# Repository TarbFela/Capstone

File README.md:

# A Temperature Programming Power & Control System for Desorption Energy Measurement Experiments

This is my electrical & computer engineering capstone as well as my honors thesis at the University of Maine. The hardware includes a number of power cards driven by PWM signals from a control board. Another board provides a serial interface to a Balzers mass spectrometer QMS 112 interface. The software for this project is largely written for the RP2350 microcontroller (like that found on the Raspberry Pi Pico 2) on a Pimoroni PGA2350 devboard/daughtercard. The PGA2350 plugs into the controller motherboard called ADPC for "Analog and Digital Processing and Control". This board incorporates, in addition to other instrumentation, MCP3462R and MCP3562R ADCs and an ADA4255 PGIA; all three of these provide SPI interfaces. I'm writing drivers for these devices which can be found in `src2/`. Functionalities are loosely (and currently rather haphazardly, with deprecation, poor compartmentalization, etc) broken out into separate headers/source files. 

I'll probably post hardware files somewhere at some point. The READMEs are currently acting as in-progress note-taking and as in-progress documentation. This project is meant to be used after I graduate by researchers in the Frederick Lab at FIRST. The code is roughly written with extensibility in mind.

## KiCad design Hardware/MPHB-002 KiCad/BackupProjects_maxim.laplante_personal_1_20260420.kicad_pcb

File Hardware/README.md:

# Temperature Programming & Control System Hardware

This is a collection of hardware documentation and resources. EasyEDA projects are downloaded and have been parsed by KiCad (do _not_ attempt to fabricate from these KiCad projects; fonts, etc have _not_ carried over). All datasheets used have been added. Any written hardware documentation is included.

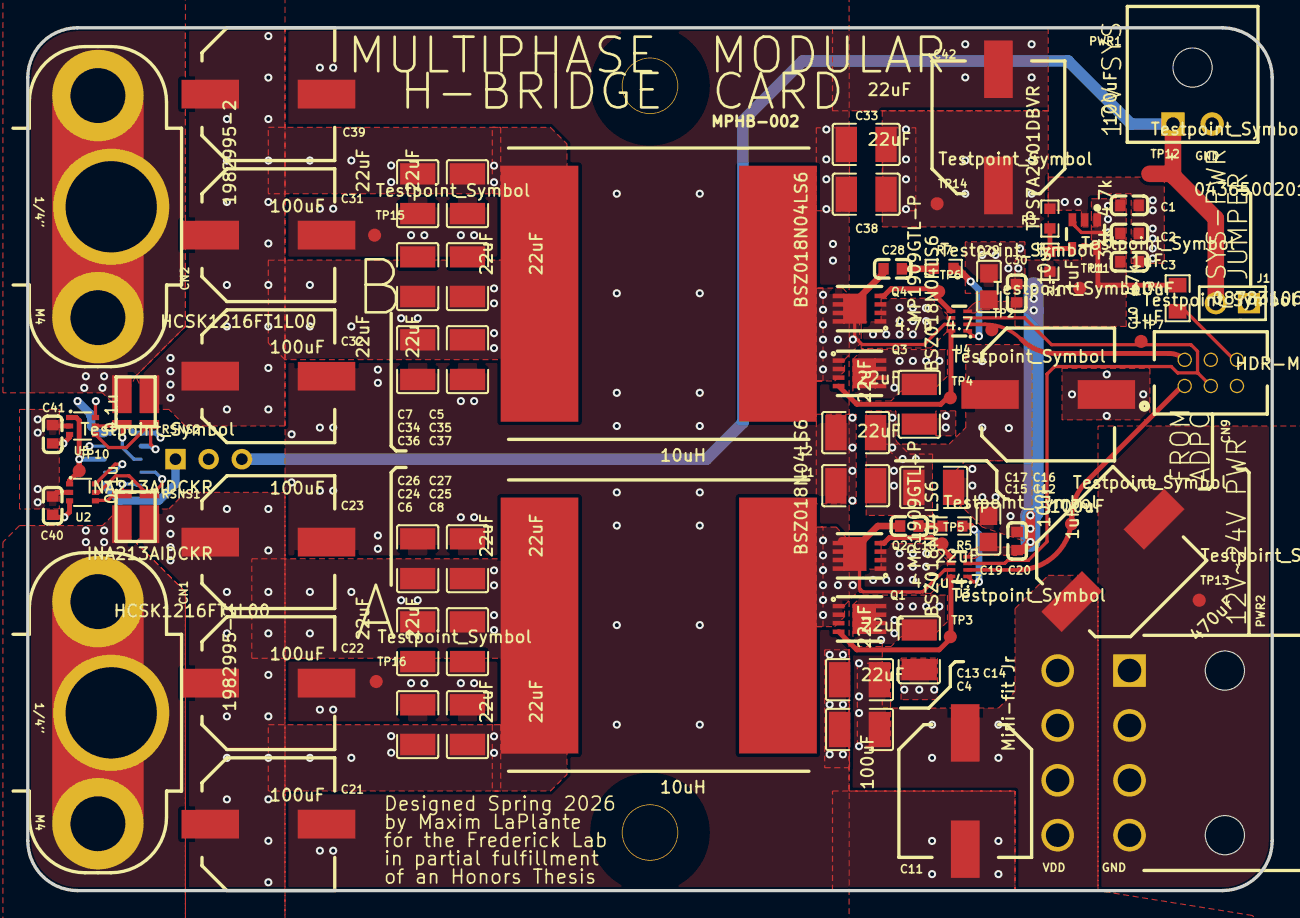
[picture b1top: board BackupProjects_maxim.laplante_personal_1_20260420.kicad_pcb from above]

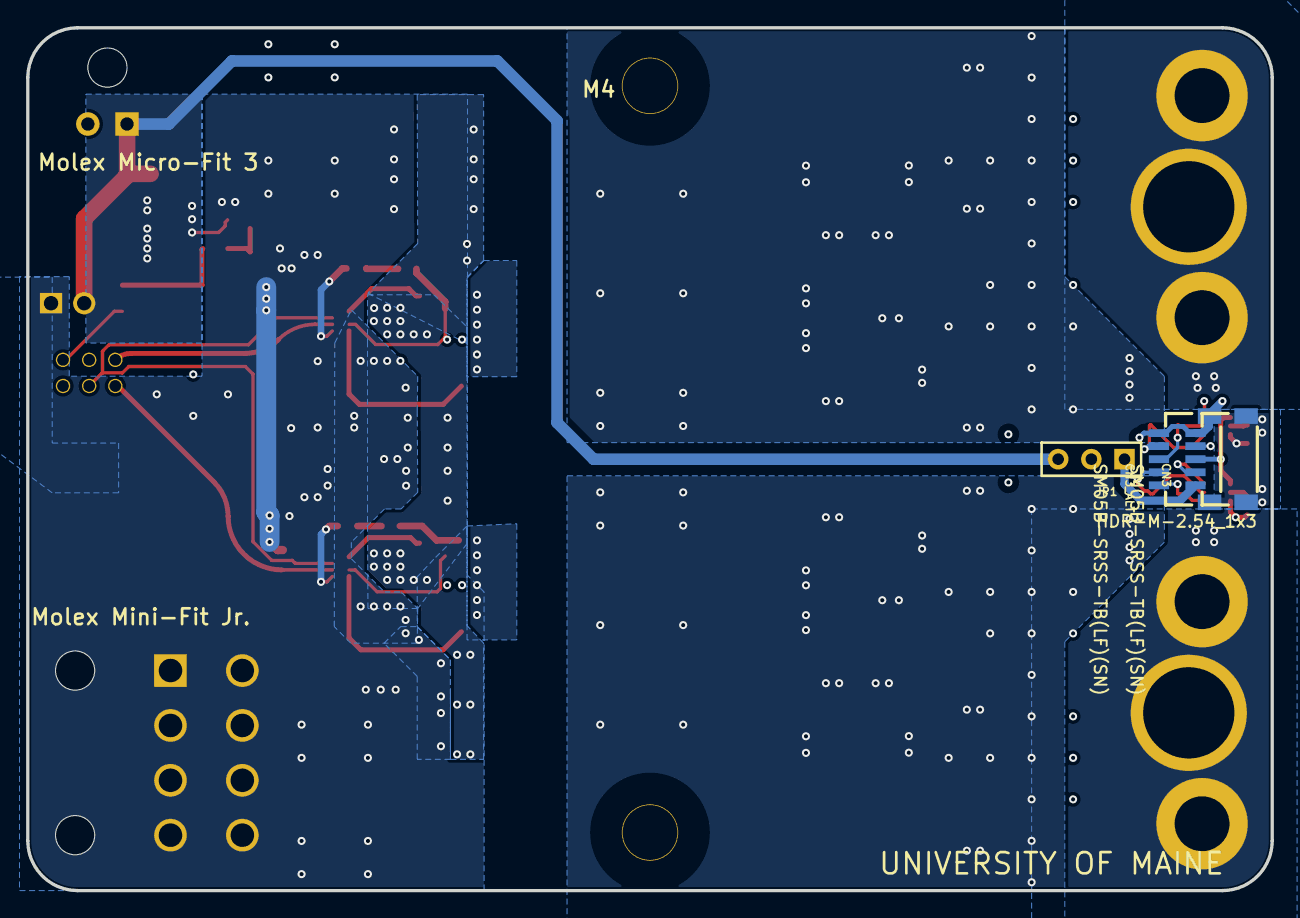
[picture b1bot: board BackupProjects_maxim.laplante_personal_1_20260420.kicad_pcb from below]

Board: 4 copper layers, 95.2 x 66.0 mm, 87 parts (3 on the bottom side), 32 nets.

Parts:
C1, C3, C20, C30: 1uF; C0603
C2: 10uF; C0603
C4, C5, C6, C7, C8, C12, C13, C14, C15, C16, C17, C24, C25, C26, C27, C33, C34, C35, C36, C37, C38: 22uF; C1210
C9: 470uF; APD_CAP_1012
C10, C11, C21, C22, C23, C31, C32, C39, C42: 100uF; APD_CAP_1012
C18, C28: 4.7u; C0603
C19, C29: 10uF; C0805
C40, C41: 0.1u; C0603
CN1, CN2: 1982995-2
CN3, CN3_ALT: SM05B-SRSS-TB(LF)(SN); CONN-SMD_SM05B-SRSS-TB
CN9: 0878310641
J1: HDR-M-2.54_1x2; HDR-M-2.54_1X2
JP1: HDR-M-2.54_1x3; HDR-M-2.54_1X3
L1, L2: 10uH; SRP2313AA
PWR1: 0436500201
PWR2: Mini-fit Jr; 0039301080
Pad_gge22614: Pad_gge22614
Pad_gge22653: Pad_gge22653
Pad_gge24533: Pad_gge24533
Pad_gge33304: Pad_gge33304
Q1, Q2, Q3, Q4: BSZ018N04LS6; PG-TSDSON-8_L3.3-W3.3-P0.65-BL
R1: 33k; R0603
R3: 4.7k; R0603
R4: 47k; R0805
R5, R7: 4.7; R0603
RSNS1, RSNS2: HCSK1216FT1L00; HCSK1216
TP1, TP2, TP3, TP4, TP5, TP6, TP7, TP10, TP11, TP12, TP13, TP14, TP15, TP16: Testpoint_Symbol; TP_TOUCH
U1: TPS7A2401DBVR; SOT-23-5_L2.9-W1.6-P0.95-LS2.8-BR
U2, U5: INA213AIDCKR; TSSOP-6_L2.0-W1.3-P0.65-LS2.0-BR
U3, U4: MP1909GTL-P; SOT-583-8_L2.1-W1.6-P0.50-LS1.6-BL

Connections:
A_OUT: CN1.1, RSNS1.2
A_OUT_FILT: C6.2, C8.2, C21.P, C22.P, C23.P, C24.2, C25.2, C26.2, C27.2, L1.2, RSNS1.1
A_SNS_HI: CN3_ALT.2, RSNS1.3, U2.5
A_SNS_LO: CN3_ALT.1, RSNS1.4, U2.4
B_OUT: CN2.1, RSNS2.1
B_OUT_FILT: C5.2, C7.2, C31.P, C32.P, C34.2, C35.2, C36.2, C37.2, C39.P, L2.2, RSNS2.2
B_SNS_HI: CN3_ALT.4, RSNS2.4, U5.4
B_SNS_LO: CN3_ALT.3, RSNS2.3, U5.5
C28_1: C28.1, R7.2
CN9_6: CN9.6, R4.1
DRVH_A: Q1.4, TP3.1, U3.8
DRVL_A: Q2.4, TP5.1, U3.5
GD_PWM_A: CN9.1, TP1.1, U3.2
GD_PWM_C: CN9.2, TP2.1, U4.2
GND: C1.1, C2.1, C3.1, C4.1, C5.1, C6.1, C7.1, C8.1, C9.N, C10.N, C11.N, C12.1, C13.1, C14.1, C15.1, C16.1, C17.1, C19.1, C20.1, C21.N, C22.N, C23.N, C24.1, C25.1, C26.1, C27.1, C29.1, C30.1, C31.N, C32.N, C33.1, C34.1, C35.1, C36.1, C37.1, C38.1, C39.N, C40.1, C41.1, C42.N, CN3.5, CN3.6, CN3.7, CN3_ALT.5, CN3_ALT.6, CN3_ALT.7, CN9.4, PWR1.2, PWR2.1, PWR2.2, PWR2.3, PWR2.4, Q2.1, Q2.2, Q2.3, Q4.1, Q4.2, Q4.3, R3.1, TP13.1, TP15.1, TP16.1, U1.2, U2.2, U3.6, U4.6, U5.2
HIGH_GATE_C: Q3.4, TP4.1, U4.8
I_SNS_A_OUT: CN3.2, U2.6
I_SNS_B_OUT: CN3.4, U5.6
I_SNS_REF_IN: CN3.3, TP10.1, U2.1, U5.1
I_SNS_VCC: C40.2, C41.2, JP1.2, U2.3, U5.3
I_SNS_VCC_IN: CN3.1, JP1.1
LOW_GATE_C: Q4.4, TP6.1, U4.5
PH_EN: CN9.3, TP7.1, U3.3, U4.3
R5_2: C18.1, R5.2
R7_1: R7.1, U4.1
REG_FB: R1.1, R3.2, U1.4
SW_A: C18.2, L1.1, Q1.1, Q1.2, Q1.3, Q2.5, Q2.6, Q2.7, Q2.8, Q2.9, U3.7
SW_C: C28.2, L2.1, Q3.1, Q3.2, Q3.3, Q4.5, Q4.6, Q4.7, Q4.8, Q4.9, U4.7
U3_1: R5.1, U3.1
VCC: C1.2, C2.2, J1.2, JP1.3, PWR1.1, TP12.1, U1.1, U1.3
VDD: C4.2, C9.P, C10.P, C11.P, C12.2, C13.2, C14.2, C15.2, C16.2, C17.2, C33.2, C38.2, C42.P, J1.1, PWR2.5, PWR2.6, PWR2.7, PWR2.8, Q1.5, Q1.6, Q1.7, Q1.8, Q1.9, Q3.5, Q3.6, Q3.7, Q3.8, Q3.9, TP14.1
V_GDRV: C3.2, C19.2, C20.2, C29.2, C30.2, R1.2, R4.2, TP11.1, U1.5, U3.4, U4.4

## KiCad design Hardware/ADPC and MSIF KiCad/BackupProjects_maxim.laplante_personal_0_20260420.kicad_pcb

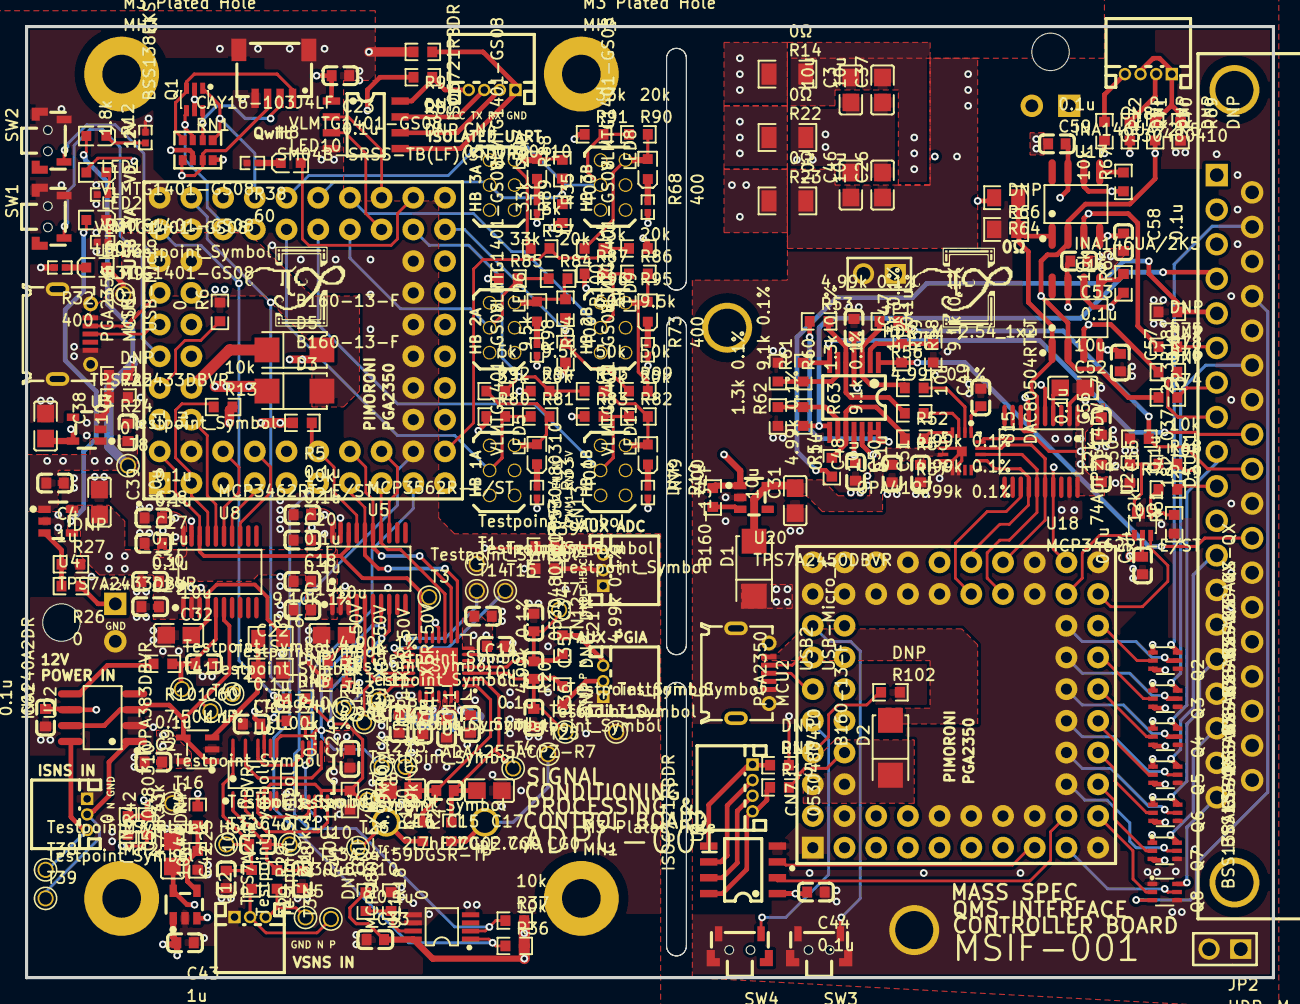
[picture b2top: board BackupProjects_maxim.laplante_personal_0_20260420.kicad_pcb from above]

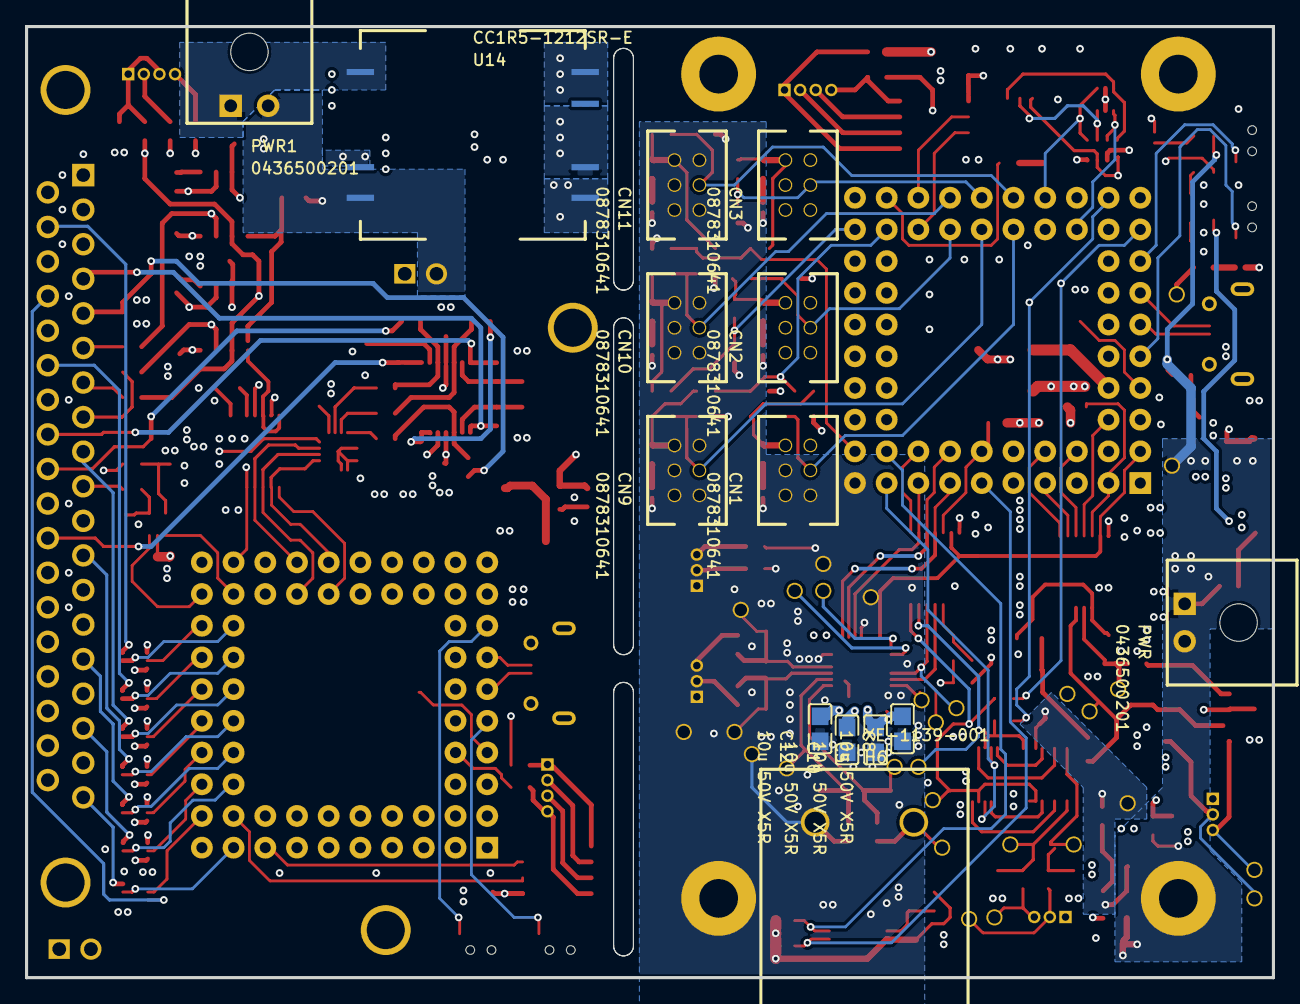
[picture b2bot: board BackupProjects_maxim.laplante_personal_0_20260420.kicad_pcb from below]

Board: 4 copper layers, 99.9 x 76.2 mm, 269 parts (14 on the bottom side), 217 nets.

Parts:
C1, C4, C43: 1u; C0603
C2, C13, C18, C19, C20, C21, C23, C24, C27, C28, C29, C30, C33, C44, C45, C47, C48, C51, C53, C54, C55, C56, C57, C58, C59, C61: 0.1u; C0603
C3, C25, C26, C31, C37, C38, C39, C46, C52: 10u; C0805
C5, C8, C10, C12: 10u 50V X5R; C0805
C6, C7, C9, C11: 0.1u X5R 50V; C0603
C14, C22, C32, C49, C50: 10u; C0603
C15: 270pF CG0; C0603
C16, C17: 2.7nF CG0; C0805
C34, C35, C36: DNP; C0603
C40, C60: 1nF; C0603
C41, C42: 10nF; C0603
CN1, CN2, CN3, CN9, CN10, CN11: 0878310641
CN4, CN7, CN8: 0530480410; CONN-TH_8P-P1.25_0530480610
CN5, CN6, CN12, CN13: 0530480310; CONN-TH_8P-P1.25_0530480410
D1, D2, D3, D5: B160-13-F; SMA_L4.3-W2.6-LS5.2-RD
DSUB1: 182-037-213R181; DB37-TH_182-037-213R181
H6: XE-1139-001; CONN-TH_XE-1139-001
H8: SM04B-SRSS-TB(LF)(SN)(P); CONN-SMD_4P-P1.00_SM04B-SRSS-TB-LF-SN
JP1, JP2: HDR-M-2.54_1x2; HDR-M-2.54_1X2
LED1, LED2, LED3, LED4, LED5, LED6, LED7, LED8, LED9, LED10, LED11: VLMTG1401-GS08; LED0603-RD_GREEN
MCU1, MCU2: PGA2350
MH1, MH2, MH3, MH4: M3 Plated Hole; M3 PLATED HOLE
PWR, PWR1: 0436500201
Pad_gge97344: Pad_gge97344
Pad_gge97365: Pad_gge97365
Q1: BSS138BKS,115; SOT-363_L2.0-W1.3-P0.65-LS2.1-BR
Q2, Q3, Q4, Q5, Q6, Q7, Q8: BSS138AKS-QX; SOT-363_L2.1-W1.3-P0.65-LS2.1-BL
R1, R2, R20, R21, R52, R53, R54, R55, R56, R57: 4.99k 0.1%; R0603
R3, R4: 4.90k 1%; R0603
R5, R13, R36, R37, R48, R49, R65, R67: 10k; R0603
R6, R18, R39, R47: 0; R0603_NEW
R8, R9, R11, R15, R19, R40, R43, R102: DNP; R0603_NEW
R10, R25, R27, R41, R69, R70, R71, R72, R74, R75, R76: DNP; R0603
R12: 1.8k; R0402
R14, R22, R23: 0Ω; R1206
R16: 9.10k 1%; R0805
R17: 1.00k 1%; R0805
R24, R26, R42, R46: 0; R0603
R28, R29: 2.10k 1%; R0603_NEW
R30, R31, R38: 60; R0402
R32, R33, R34, R35, R68, R73, R79: 400; R0402
R44: 4.7k; R0603
R45, R80, R83, R85, R87, R89, R91: 33k; R0603
R50, R51: 12k; R0603
R58, R61, R63: 9.1k 0.1%; R0603
R59, R60, R62: 1.3k 0.1%; R0603
R64: 0Ω; R0805_1
R66: DNP; R0805_1
R77, R78: 0Ω; R0603
R81, R82, R84, R86, R88, R90: 20k; R0603
R92, R97, R100: 5k; R0603
R93, R96, R99: 50k; R0603
R94, R95, R98: 9.5k; R0603
R101: 7.50k 1%; R0603_NEW
RN1: CAY16-103J4LF; RES-ARRAY-SMD_0603-8P-L3.2-W1.6-BL
SW1, SW2, SW3, SW4: TS24CA; SW-SMD_2P-TS24CA
T1, T2, T3, T4, T5, T6, T7, T8, T9, T10, T11, T12, T13, T14, T15, T16, T25, T26, T27, T28, T29, T30, T31, T32, T38, T39, T40, T41: Testpoint_Symbol; TESTPOINT_FOOTPRINT
U1: ADA4255ACPZ-R7; QFN-28_L5.0-W5.0-P0.50-TL-EP3.1
U2, U13: ISO6721RBDR; SOP-8_L4.9-W3.9-P1.27-LS6.0-BL_ISO6721RBDR
U3, U4: TPS7A2433DBVR; SOT-23-5_L2.9-W1.6-P0.95-LS2.8-BR
U5: MCP3562R-E/ST; TSSOP-20_L6.5-W4.4-P0.65-LS6.4-BL
U6: LT1997HMS-1#TRPBF; MSOP-16_12P-L4.0-W3.0-P0.50-LS4.9-BL
U8, U18: MCP3462RT-E/ST; TSSOP-20_L6.5-W4.4-P0.65-LS6.4-BL
U9: OPA383DBVR; SOT-23-5_L3.0-W1.7-P0.95-LS2.8-BL
U10: TS3A24159DGSR-TP; MSOP-10_L3.0-W3.0-P0.50-LS4.9-BL
U11: MCP9808-E/MS; MSOP-8_L3.0-W3.0-P0.65-LS4.9-BL
U12: TPS7A2401DBVR; SOT-23-5_L2.9-W1.6-P0.95-LS2.8-BR
U14: CC1R5-1212SR-E; CC1R5-E MODULE
U15: DAC80504RTET; WQFN-16_L3.0-W3.0-P0.50-TL-EP0.8
U16, U17: INA146UA/2K5; SOIC-8_L4.9-W3.9-P1.27-LS6.0-BL
U19: OPA4197; TSSOP-14_L5.0-W4.4-P0.65-LS6.4-BL
U20: TPS7A2450DBVR; SOT-23-5_L2.9-W1.6-P0.95-LS2.8-BR
U21: 74AUP2G14DW-7; SOT-363_L2.0-W1.3-P0.65-LS2.1-BR
U22: INA240A2DR; SOIC-8_L4.9-W3.9-P1.27-LS6.0-BL
USB1, USB2: USB-Micro_1; MICRO-USB-SMD_5P-P0.65-H-F_C10418

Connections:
3V3: C13.2, C14.2, C20.2, C21.2, C23.2, C24.2, C27.2, C28.2, C33.2, C38.2, D5.2, LED2.2, Q1.2, Q1.5, R5.2, R8.2, R13.2, R18.1, R36.2, R37.2, RN1.2, RN1.4, T1.1, U1.7, U2.1, U3.5, U5.20, U8.20, U10.1, U11.8
3V3A: C2.2, C5.2, C6.2, C7.2, C8.2, C18.2, C19.2, C29.2, C30.2, C39.2, C61.2, LED3.2, T2.1, U1.23, U1.25, U4.5, U5.1, U8.1, U9.5, U22.6
3V3_IF: C44.2, C54.2, C55.2, C56.2, MCU2.3V3, R15.2, U13.1, U15.16, U18.1, U18.20, U21.5
5V_IF: C31.2, C50.2, C51.2, D1.2, U15.7, U20.5
10V: C25.2, C45.2, R45.2, T16.1, U6.11, U12.5
10V_EN: R41.1, R42.2, U12.3
10V_FB: R44.2, R45.1, U12.4
12VIN: C1.2, C4.2, C43.2, LED1.2, PWR.1, R24.1, R26.1, R42.1, T8.1, U3.1, U4.1, U12.1
12VIN_MSIF: PWR1.1, U14.1
+12V_IF: C3.2, C37.2, C47.2, C53.2, C59.2, R10.2, R14.2, U16.7, U17.7, U19.4, U20.1
-12V_IF: C26.1, C46.1, C48.2, C57.1, C58.1, R23.2, U16.4, U17.4, U19.11
ADC_16_IRQ: MCU1.2, R13.1, U8.17
ADC_16_MCLK: MCU1.1, T3.1, U1.14, U5.18, U8.18
ADC_16_REFOUT: C32.2, R16.2, U8.4
ADC_16_SPI_CS: MCU1.5, U8.13
ADC_16_SPI_SCK: MCU1.6, U8.14
ADC_16_SPI_SDI: MCU1.3, U8.15
ADC_16_SPI_SDO: MCU1.0, U8.16
ADC_24_IRQ: MCU1.9, R5.1, U5.17
ADC_24_SPI_CS: MCU1.13, U5.13
ADC_CH0: T12.1, U1.20, U5.5
ADC_CH1: T13.1, U1.19, U5.6
ADC_REFOUT: C22.2, R4.2, U5.4
CN7_1: CN7.1, R11.1, U13.5
CN7_2: CN7.2, U13.6
CN7_3: CN7.3, U13.7
CN7_4: CN7.4, R15.1, U13.8
D1_1: D1.1, D2.1, MCU2.VBUS
DSUB1_6: DSUB1.6, R75.2
DSUB1_7: DSUB1.7, R74.2
DSUB1_8: DSUB1.8, R76.2
GND: C1.1, C2.1, C4.1, C5.1, C6.1, C7.1, C8.1, C9.1, C10.1, C11.1, C12.1, C13.1, C14.1, C16.2, C17.1, C18.1, C19.1, C20.1, C21.1, C22.1, C23.1, C24.1, C25.1, C27.1, C28.1, C29.1, C30.1, C32.1, C33.1, C34.1, C36.2, C38.1, C39.1, C41.2, C42.1, C43.1, C45.1, C60.1, C61.1, CN1.4, CN2.4, CN3.4, CN5.1, CN6.1, CN9.4, CN10.4, CN11.4, CN12.1, CN13.1, H8.4, H8.5, H8.6, MCU1.GND, PWR.2, R3.1, R6.2, R9.2, R12.2, R17.1, R19.2, R25.2, R27.2, R30.2, R31.2, R32.2, R33.2, R34.2, R35.2, R38.2, R41.2, R44.1, R46.2, R68.2, R73.2, R79.2, R80.1, R83.1, R85.1, R87.1, R89.1, R91.1, R94.1, R95.1, R98.1, SW1.2, SW1.3, SW2.2, SW2.3, T10.1, U1.6, U1.22, U2.4, U3.2, U4.2, U5.2, U5.3, U5.19, U6.8, U8.2, U8.3, U8.19, U9.2, U10.6, U11.4, U11.5, U11.6, U12.2, U22.2, USB1.5, USB1.SH0
GND_IN_MSIF: JP1.2, PWR1.2, U14.3
I2C_HEADER_SCL: MCU1.43, Q1.4, RN1.7
I2C_HEADER_SDA: MCU1.42, Q1.1, RN1.5
INAMP_GPIO2_CALIB_BUSY: MCU1.4, T15.1, U1.16
INAMP_GPIO3_FAULT: MCU1.8, T14.1, U1.15
INAMP_IN1_N: C15.1, C17.2, R2.2, T4.1, U1.2
INAMP_IN1_P: C15.2, C16.1, R1.2, T5.1, U1.1
INAMP_IN2_N: C34.2, C35.1, R21.2, T7.1, U1.4
INAMP_IN2_P: C35.2, C36.1, R20.2, T6.1, U1.3
INAMP_SPI_CS: MCU1.7, U1.11
INAMP_SPI_SCLK: MCU1.14, U1.10, U5.14
INAMP_SPI_SDI: MCU1.11, U1.9, U5.15
INAMP_SPI_SDO: MCU1.12, U1.8, U5.16
INAMP_VDDH: C9.2, C10.2, U1.26
INAMP_VOCM: R3.2, R4.1, T11.1, U1.21
INAMP_VSSH: C11.2, C12.2, U1.27, U1.29
INA_AUX_N: CN12.3, R21.1
INA_AUX_P: CN12.2, R20.1
ISOUART_RX: CN4.2, U2.6
ISOUART_TX: CN4.3, U2.7
I_AMP2_OUT_FILT: C60.2, R101.1, T41.1, U8.5
I_AMP_OUT: R101.2, U22.5
I_AMP_REF: T40.1, U8.6, U9.1, U9.4, U22.3, U22.7
LED1_1: LED1.1, R12.1
LED2_1: LED2.1, R30.1
LED3_1: LED3.1, R31.1
LED4_1: LED4.1, R32.1
LED5_1: LED5.1, R33.1
LED6_1: LED6.1, R34.1
LED7_1: LED7.1, R35.1
LED9_1: LED9.1, R73.1
LED10_1: LED10.1, R38.1
LED11_1: LED11.1, R79.1
MCU1_3V3EN: MCU1.3V3EN, R6.1
MCU1_BOOTSEL: MCU1.BOOTSEL, SW2.1
MCU1_RUN: MCU1.RUN, SW1.1
MCU2_3V3EN: MCU2.3V3EN, R102.1
MCU2_BOOTSEL: MCU2.BOOTSEL, SW3.1
MCU2_RUN: MCU2.RUN, SW4.1
MCU2_USB+: MCU2.USB+, USB2.3
MCU2_USB-: MCU2.USB-, USB2.2
MCU_3V3: D5.1, MCU1.3V3
MCU_ADC_5: MCU1.45, R40.1, R47.1
MCU_ADC_6: MCU1.46, R39.1, R43.1
MCU_INDICATOR_LED_1: LED10.2, MCU1.32
MCU_VBUS: D3.1, MCU1.VBUS
MH: DSUB1.38, DSUB1.39, MH1.1, MH2.1, MH3.1, MH4.1
MPHB_5V_1: CN1.6, LED5.2, R81.2, R92.1
MPHB_5V_1.1: CN9.6, LED11.2, R82.2, R93.2
MPHB_5V_2: CN2.6, LED6.2, R84.2, R100.1
MPHB_5V_2.1: CN10.6, LED9.2, R86.2, R99.2
MPHB_5V_3: CN3.6, LED7.2, R88.2, R97.1
MPHB_5V_3.1: CN11.6, LED8.2, R90.2, R96.2
MPHB_ISNS_N: CN6.2, T39.1, U22.1
MPHB_ISNS_P: CN6.3, T38.1, U22.8
MPHB_VDET_1: MCU1.31, R92.2, R93.1, R94.2
MPHB_VDET_2: MCU1.30, R98.2, R99.1, R100.2
MPHB_VDET_3: MCU1.17, R95.2, R96.1, R97.2
MPHB_VSNS_HI: CN5.3, R28.2, T29.1
MPHB_VSNS_LO: CN5.2, R29.2, T30.1
MSIF_ADC_CS: MCU2.37, U18.13
MSIF_ADC_IRQ: MCU2.32, U18.17
MSIF_ADC_SCK: MCU2.38, U15.13, U18.14
MSIF_AMP_EC: R65.1, U16.6, U18.5
MSIF_AMP_SCAN+: R67.1, U17.6, U18.7
MSIF_CLR_EC: MCU2.24, Q4.2
MSIF_DAC_REFO: C49.1, U15.1
MSIF_DAC_SDI: MCU2.35, U15.14, U18.15
MSIF_DAC_SDO: MCU2.36, U15.15, U18.16
MSIF_DAMP_REF: R64.1, R66.2, U16.1, U17.1, U18.6, U18.8
MSIF_EMIS_OK: MCU2.30, U21.6
MSIF_FMASS: R52.1, U15.2
MSIF_GAIN_0: MCU2.19, Q7.5
MSIF_GAIN_1: MCU2.18, Q7.2
MSIF_MODE_0: MCU2.21, Q6.5
MSIF_MODE_1: MCU2.20, Q6.2
MSIF_MODE_2: MCU2.23, Q5.5
MSIF_ON_LINE: MCU2.16, Q8.5
MSIF_RANGE_0: MCU2.22, Q5.2
MSIF_RANGE_1: MCU2.25, Q4.5
MSIF_RESET_SCAN: MCU2.26, Q3.2
MSIF_SCAN_IN_PROGRESS: MCU2.31, U21.4
MSIF_SEM: R57.1, U15.4
MSIF_SPEED_0: MCU2.27, Q3.5
MSIF_SPEED_1: MCU2.28, Q2.2
MSIF_SPEED_2: MCU2.29, Q2.5
MSIF_SPEED_3: MCU2.17, Q8.2
MSIF_SWIDTH: R55.1, U15.3
MSIF_UART_RX: MCU2.15, U13.2
MSIF_UART_TX: MCU2.14, U13.3
MSQDP_CLR_EC: DSUB1.9, Q4.6
MSQDP_DIG_GND: DSUB1.33, JP2.1
MSQDP_EC+: R71.2, R75.1, U17.3
MSQDP_EC-: R70.2, R74.1, U16.2, U17.2, U19.12
MSQDP_EC-_BUFF: R53.1, R64.2, U19.13, U19.14
MSQDP_EMIS_OK: DSUB1.10, R49.2
MSQDP_FMASS+: DSUB1.30, R58.2, U19.1
MSQDP_FMASS-: DSUB1.28, R56.1, R77.1
MSQDP_GAIN_0: DSUB1.18, Q7.3
MSQDP_GAIN_1: DSUB1.17, Q7.6
MSQDP_MODE_0: DSUB1.16, Q6.3
MSQDP_MODE_1: DSUB1.15, Q6.6
MSQDP_MODE_2: DSUB1.14, Q5.3
MSQDP_ON_LINE: DSUB1.23, Q8.3
MSQDP_RANGE_0: DSUB1.12, Q5.6
MSQDP_RANGE_1: DSUB1.11, Q4.3
MSQDP_RESET_SCAN: DSUB1.25, Q3.6
MSQDP_SCAN+: R72.2, R76.1, U16.3
MSQDP_SCAN_IN_PROGRESS: DSUB1.24, R48.2
MSQDP_SEM+: DSUB1.4, R63.2, U19.8
MSQDP_SEM-: DSUB1.5, R54.1, R78.1
MSQDP_SIG_GND: C3.1, C26.2, C31.1, C37.1, C44.1, C46.2, C47.1, C48.1, C49.2, C50.1, C51.1, C52.2, C53.1, C54.1, C55.1, C56.1, C57.2, C58.2, C59.1, DSUB1.26, JP2.2, MCU2.GND, Q2.1, Q2.4, Q3.1, Q3.4, Q4.1, Q4.4, Q5.1, Q5.4, Q6.1, Q6.4, Q7.1, Q7.4, Q8.1, Q8.4, R11.2, R22.2, R50.1, R51.1, R59.1, R60.1, R62.1, R66.1, R69.2, R77.2, R78.2, R102.2, SW3.2, SW3.3, SW4.2, SW4.3, U13.4, U15.6, U15.8, U15.9, U15.10, U15.17, U18.2, U18.19, U20.2, U21.2, USB2.5, USB2.SH0
MSQDP_SPEED_0: DSUB1.22, Q3.3
MSQDP_SPEED_1: DSUB1.21, Q2.6
MSQDP_SPEED_2: DSUB1.20, Q2.3
MSQDP_SPEED_3: DSUB1.19, Q8.6
MSQDP_SWIDTH+: DSUB1.27, R61.2, U19.7
PH_EN_A1: CN1.3, MCU1.39, R80.2, R81.1
PH_EN_A2: CN2.3, MCU1.35, R84.1, R85.2
PH_EN_A3: CN3.3, MCU1.38, R88.1, R89.2
PH_EN_B1: CN9.3, MCU1.37, R82.1, R83.2
PH_EN_B2: CN10.3, MCU1.36, R86.1, R87.2
PH_EN_B3: CN11.3, MCU1.40, R90.1, R91.2
PWM_A_1: CN1.2, MCU1.18
PWM_A_2: CN2.2, MCU1.23
PWM_A_3: CN3.2, MCU1.28
PWM_B_1: CN9.2, MCU1.20
PWM_B_2: CN10.2, MCU1.25
PWM_B_3: CN11.2, MCU1.26
PWM_C_1: CN1.1, MCU1.19
PWM_C_2: CN2.1, MCU1.22
PWM_C_3: CN3.1, MCU1.29
PWM_D_1: CN9.1, MCU1.21
PWM_D_2: CN10.1, MCU1.24
PWM_D_3: CN11.1, MCU1.27
QT_SCL: H8.1, Q1.3, RN1.8
QT_SDA: H8.2, Q1.6, RN1.6
QT_VCC: H8.3, RN1.1, RN1.3
R16_1: R16.1, R17.2, U9.3
R39_2: CN13.3, R39.2
R47_2: CN13.2, R47.2
R52_2: R52.2, R56.2, U19.3
R55_2: R53.2, R55.2, U19.5
R57_2: R54.2, R57.2, U19.10
R68_1: LED8.1, R68.1
R69_1: CN8.1, CN8.3, R69.1, R70.1
R71_1: CN8.2, R71.1
R72_1: CN8.4, R72.1
TC_N: H6.2, R2.1, T25.1
TC_P: H6.1, R1.1, T26.1
TMP_I2C_SCL: MCU1.15, R37.1, U11.2
TMP_I2C_SDA: MCU1.10, R36.1, U11.1
U2_5: CN4.1, R9.1, U2.5
U2_8: CN4.4, R8.1, U2.8
U3_3: R24.2, R25.1, U3.3
U4_3: R26.2, R27.1, U4.3
U11_7: R18.2, R19.1, U11.7
U14_2: JP1.1, U14.2
U14_4: R23.1, U14.4
U14_5: R22.1, U14.5
U14_7: R14.1, U14.7
U16_5: R65.2, U16.5
U17_5: R67.2, U17.5
U18_4: C52.1, U18.4
U19_2: R58.1, R59.2, U19.2
U19_6: R60.2, R61.1, U19.6
U19_9: R62.2, R63.1, U19.9
U20_3: R10.1, U20.3
U21_1: R49.1, R51.2, U21.1
U21_3: R48.1, R50.2, U21.3
UART_RX: MCU1.33, U2.3
UART_TX: MCU1.34, U2.2
USB2_1: D2.2, USB2.1
USB_D+: MCU1.USB+, USB1.3
USB_D-: MCU1.USB-, USB1.2
VSNS_AMP_3K_N: U6.12, U10.5
VSNS_AMP_3K_P: U6.5, U10.7
VSNS_AMP_7K5_N: U6.14, U10.2
VSNS_AMP_7K5_P: U6.3, U10.10
VSNS_AMP_GAIN_SEL: MCU1.16, U10.4, U10.8
VSNS_AMP_OUT: R40.2, T27.1, U5.7, U6.9, U10.3
VSNS_AMP_REF: R43.2, R46.1, T28.1, U5.8, U6.6, U6.7, U10.9
VSNS_FILT_N: C40.1, C42.2, R29.1, T32.1, U6.16
VSNS_FILT_P: C40.2, C41.1, R28.1, T31.1, U6.1
V_USB: D3.2, LED4.2, T9.1, USB1.1

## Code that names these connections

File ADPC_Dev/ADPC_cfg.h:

// Pin definitions for the ADPC-001 board (motherboard) using the Pimoroni PGA2350 daughter board

#include "hardware/spi.h"
#include "hardware/pwm.h"
#include "hardware/i2c.h"

// MCU LED pin on ADPC
#define ADPC_PIN_LED        32

// 16-bit MCP3462R ADC: performs ISNS
#define ADC_0_PIN_MOSI      3
#define ADC_0_PIN_MISO      0
#define ADC_0_PIN_CS        5
#define ADC_0_PIN_SCK       6
#define ADC_0_PIN_IRQ       2
#define ADC_0_SPI           spi0

// 24-bit MCP3562R ADC: performs TSNS and VSNS functionalitites
#define ADC_1_PIN_MOSI      11
#define ADC_1_PIN_MISO      12
#define ADC_1_PIN_CS        13
#define ADC_1_PIN_SCK       14
#define ADC_1_PIN_IRQ       9
#define ADC_1_SPI           spi1

#define ADC_MCLK_PIN        1


// ADA4255 programmable-gain instrumentation amplifier: TSNS amplifier
// Sits on same SPI bus as ADC 1
#define PGIA_PIN_MOSI       ADC_1_PIN_MOSI
#define PGIA_PIN_MISO       ADC_1_PIN_MISO
#define PGIA_PIN_CS         7
#define PGIA_PIN_SCK        ADC_1_PIN_SCK
#define PGIA_SPI            ADC_1_SPI

#define PGIA_PIN_GPIO3_FAULT 8
#define PGIA_PIN_GPIO2_CALIB 4

// MCP9808 I2C temperature sensor
#define TMP_SNS_PIN_SDA 10
#define TMP_SNS_PIN_SCL 15
#define TMP_SNS_I2C i2c1

// TS3A24159 Analog Switch for VSNS LT1997 Amplifier Gain Selection
#define VSNS_AMP_GAIN_SEL_PIN   16
//todo: move the following defs to a more appropriate file?
#define VSNS_AMP_GAIN_SEL_0V196 0
#define VSNS_AMP_GAIN_SEL_0V476 1

// MPHB-002 Signals
// Headers labelled as follows (a carry-over from MPHB-001 which had four bucks per board (ABCD) as opposed to two
//      HB-1A --> PWM_AC_1
//      HB-1B --> PWM_BD_1
//      HB-2A --> PWM_AC_2
//      HB-2B --> PWM_BD_2
//      HB-3A --> PWM_AC_3
//      HB-3B --> PWM_BD_3

#define PWM_A_1_PIN 18
#define PWM_C_1_PIN 19
#define PWM_B_1_PIN 20
#define PWM_D_1_PIN 21
#define PWM_C_2_PIN 22
#define PWM_A_2_PIN 23
#define PWM_D_2_PIN 24
#define PWM_B_2_PIN 25
#define PWM_B_3_PIN 26
#define PWM_D_3_PIN 27
#define PWM_A_3_PIN 28
#define PWM_C_3_PIN 29

#define	PH_EN_A2_PIN 35
#define	PH_EN_B2_PIN 36
#define	PH_EN_B1_PIN 37
#define	PH_EN_A3_PIN 38
#define	PH_EN_A1_PIN 39
#define	PH_EN_B3_PIN 40

#define PWM_A_1_CHAN PWM_CHAN_A
#define PWM_C_1_CHAN PWM_CHAN_B
#define PWM_B_1_CHAN PWM_CHAN_A
#define PWM_D_1_CHAN PWM_CHAN_B
#define PWM_C_2_CHAN PWM_CHAN_A
#define PWM_A_2_CHAN PWM_CHAN_B
#define PWM_D_2_CHAN PWM_CHAN_A
#define PWM_B_2_CHAN PWM_CHAN_B
#define PWM_B_3_CHAN PWM_CHAN_A
#define PWM_D_3_CHAN PWM_CHAN_B
#define PWM_A_3_CHAN PWM_CHAN_A
#define PWM_C_3_CHAN PWM_CHAN_B

#define PWM_AC_1_SLICE 1
#define PWM_BD_1_SLICE 2
#define PWM_AC_2_SLICE 3
#define PWM_BD_2_SLICE 4
#define PWM_BD_3_SLICE 5
#define PWM_AC_3_SLICE 6

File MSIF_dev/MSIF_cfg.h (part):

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#define MSIF_DAC_CS_PIN         42          // existing bodge to U15 pins 11/12 (shorted)
#define MSIF_DAC_LDAC_PIN       MSIF_DAC_CS_PIN  // same GPIO 42; driver skips duplicate init
#define MSIF_DAC_SCK_PIN        38          // shared with ADC SCK
#define MSIF_DAC_SDI_PIN        35          // shared with ADC SDI (MOSI)
#define MSIF_DAC_SDO_PIN        36          // shared ADC/DAC SDO (MISO)
#define MSIF_DAC_BAUD_HZ        1000000u    // 1 MHz conservative; DAC80504 tolerates up to 50 MHz

// ==========================================================================
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// INA146 (U16/U17) difference amps → MCP3462RT VIN+/VIN-.
//
// Shares SPI0, SCK (38), MOSI (35), MISO (36) with the DAC80504; only
// MSIF_ADC_CS_PIN (37) is unique. SPI mode is INCOMPATIBLE with the DAC
// (DAC needs mode 1, ADC needs mode 0) — msif_adc.c and msif_analog.c both
// call spi_set_format() at the top of every bus-touching public function.
//
// MSIF_ADC_IRQ_PIN (GPIO 32) is the MCP3462RT's nIRQ output. Per the driver
// README, this line MUST be pulled high externally for the ADC to convert;
// the firmware also enables the RP2350 internal pull-up as a belt-and-braces
// defense, but a missing external pull would leave the converter silent.
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// injecting a known DC voltage at QDP EC- and watching for a response;
// if it's silent, cycle through the other MUX pairings in msif_adc.c.
// ==========================================================================
#define MSIF_ADC_CS_PIN         37
#define MSIF_ADC_IRQ_PIN        32
#define MSIF_ADC_SPI            MSIF_DAC_SPI    // same spi0 peripheral
#define MSIF_ADC_V_REF          2.4f            // MCP3462R internal reference

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// see schematic note about ADPC/MSIF supply rail dependency.
// ==========================================================================
#define MSIF_UART                       uart0
#define MSIF_UART_TX_PIN                12
#define MSIF_UART_RX_PIN                13
#define MSIF_UART_BAUD                  115200u

#endif
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
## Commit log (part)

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2025-12-09 Copied files
2025-12-11 Manual ADC buffer fills [bug: ADC FIFO not flushed between batches]
2025-12-11 Cleanup
2025-12-11 PI control with fixed current target
2025-12-11 Working CL control
2025-12-11 Integer PI controller [Bug: integrator bounded too hard]
2025-12-11 Integer PI control (roughly 100Hz)
2025-12-12 Working ADC round-robin and DMA daisy-chain
2025-12-12 Broken Buggy PI control
2025-12-12 Inelegant PI control re-implemented
2025-12-12 Reorganized ADC and DMA inits into dedicated header
2025-12-12 ADC/DMA stop/start commands working
2025-12-13 Working PI control [BUG: pulse-train noise appears]
2025-12-15 IRQ CL Control
2025-12-16 [WIP] Sweep
2025-12-17 Network Analyzer Mode
2025-12-17 Mutex and INA236 function
2025-12-17 [WIP] Cleaner OVFFSET sweep
2025-12-17 Some stuff??
2025-12-17 Starting TC conversions
2025-12-17 Temperature Readings Kind of Accurate?
2025-12-17 Adapted W25 driver from previous work
2025-12-17 Datalogging and reading
2025-12-17 Fixed sector erase to align with page-sector alignemnt
2025-12-17 Working for review
2026-01-22 Working version before breaking stuff
2026-01-22 test commit?
2026-01-22 test commit
2026-01-22 final test of git bs
2026-01-23 Really stupid bug fix in flash write
2026-01-23 added PWM mode for debugging measurements
2026-01-23 PWM Current Readouts for G=150 Diffamp
2026-01-23 Updated CL control for G=150 setup [temporary ISNS regime]
2026-02-02 UI for arbitrary address and string writing testing
2026-02-02 saving [BUGGY] interrupt-based logging regime
2026-02-02 Choose whether to read or not in arbitrary UI mode
2026-02-02 Added CS latching time (arbitrary 10us)
2026-02-02 Working repeatable writes
2026-02-03 Rudimentary Datalogging Working [BUG: jumpy TC measurement]
2026-02-03 Moving functions around
2026-02-05 Stickier setpoints
2026-02-05 Data analysis for datalogged and DAD2
2026-02-11 Data parsing stuff
2026-02-11 UI Bug Fixes and Updated Current Control Circuit
2026-02-26 Started work on MCP356xR driver (testing on MCP3462R)
2026-02-26 Data analysis & up-to-date
2026-02-26 Arbitrary cfg write function, tested. Status byte dubious.
2026-02-26 Piecing together ADC reading code
2026-02-26 Added MUX Input Select headers and docs.
2026-02-26 Progress of driver. Still not getting real ADC readings.
2026-03-03 Capstone revs: calculating dT/dt (sloppy, on command)
2026-03-03 comments
2026-03-08 Wrote literal test script. Works.
2026-03-14 Two phase and ADC driver development
2026-03-14 Copied registers and started fields from datasheet.
2026-03-14 ADA4255 driver development. Succesfully read config register and got expected default val (0x4).
2026-03-14 Removed needless sleep
2026-03-14 IRQ Pullup Note
2026-03-14 ADA4255 Driver Readme started.
2026-03-14 Top-level README started. overview.
2026-03-14 Added symlink for driver directory.
2026-03-19 Adding ADC0, PGIA GPIO, and TMP_SNS pin defs
2026-03-20 Added test for ADC IRQ pin
2026-03-20 [WIP] Started PIO for ADC continuous reading.
2026-03-21 broken, going back
2026-03-21 [WORKS] Literal, polling implementation of continuous conversion reads.
2026-03-22 Started anew on the PIO for ADC reading. [Compiles]
2026-03-22 Oops forgot the PIO files!
2026-03-22 [WIP] Program to read samples with PIO and DMA. Times out. Needs scoping!
2026-03-22 Updated pin defs for ADPC and Breadboard
2026-03-22 DMA IRQ clear.
2026-03-22 [WORKS] Breadboarding continuous conversions with GPIO nIRQ polling
2026-03-22 [Compiles] Replaced pico W with pico 2 on breadboard for PIO wait jmppin.
2026-03-22 [WORKS] 100 samples with PIO, DMA and MCP ADC in continuous mode!!
2026-03-23 Swapped CS literal pin for macro
2026-03-25 [WIP] Started DMA daisy chain setup.
2026-04-10 Started MSIF.
2026-04-11 Fixed comment.
2026-04-11 Docs
2026-04-11 Docs render
2026-04-11 Updated git instructions.
2026-04-13 [WIP] 100-batch reads.
2026-04-13 [WORKS] daisy-chained DMAs
2026-04-13 Defined DMA_BUFF_SIZE and started align() work
2026-04-13 [WORKS] Using alignment and DMA Ring feature. No need for write-address resets!
2026-04-13 Moved mcp pio files to driver directory.
2026-04-13 [oops] Added mcp pio files *back* to git!
2026-04-13 [WIP: bad adc vals] ADPC_ADC starting
2026-04-13 [Works] Fixed printf issue, teehee!
2026-04-13 Defs for scan delays
2026-04-13 [untested new funcs] Bringing in configuration functions
2026-04-13 Replaced literals with macros in config regs.
2026-04-13 Started configuration function
2026-04-13 Fixed number of cfgs and included prototype in header file
2026-04-13 Starting testing for configuration function
2026-04-13 Rearranged project structure so that ADPC files are in ADPC_Dev
2026-04-14 Re-rendered Schematics (PNG)
2026-04-14 Template extensions
2026-04-14 [fixed] Template extensions
2026-04-16 [wip] prepping for a checkout...
2026-04-16 [works, wip] Fixing ADPC_ADC init funcs
2026-04-16 [works, wip] Fixing config
2026-04-16 [works, wip] mcp_configure() works, I think!
2026-04-17 [works] Scan mode!
2026-04-17 [broken] Trying to set up cfg struct and usage.
2026-04-17 [still works]
2026-04-17 [still works] expanded struct
2026-04-17 [still works] Changed configure() prototype to take struct pointer
2026-04-17 [*seems* to work] Configurable inputs
2026-04-17 [works] removed prints in configure()
2026-04-17 Driver documentation (PIO, etc)
2026-04-17 [untested] Default config function
2026-04-17 [untested] Changed adc_start to use mcp_write.
2026-04-19 ADPC Pins Documentation Start
2026-04-19 Pin functions listed
2026-04-19 Decided SPI Flash Fix pin/connector assigments and next steps. Wrote explainer text.
2026-04-20 [works] Streams ADC batch data over USB CDC mode
2026-04-20 Script to perform serial interface with mcp test program.
2026-04-20 Quick documentation
2026-04-20 Added file logging (CSV)
2026-04-20 Added graphing and file logging.
2026-04-20 Easier streaming without reboots; user input for byte count.
2026-04-20 [wip, works] literal SPI writes seem to work repeatably. Need to compartmentalize and sort out why configure() doesn't work.
2026-04-20 Destinatin for ADC logging files
2026-04-20 Moving in hardware documentation
2026-04-20 ADPC and MSIF Schematics
2026-04-20 Added EDA Projects (EasyEDA zips and KiCad versions of those zips)
2026-04-20 Added EasyEDA Downloaded Projects
2026-04-20 README
2026-04-21 [fixed] Replaced **ADC_CS** with **PGIA_CS**. Stupid!
2026-04-21 [works] Input MUX and gain setting functions
2026-04-21 Added PGIA inits
2026-04-21 Sorting log file list options
2026-04-21 Added PGIA driver
2026-04-21 Set timer and dly to 0 for scan mode.
2026-04-21 Removed row printing
2026-04-21 [Verified] Supplying MCLK to ADCs.
2026-04-21 Moving full-board data streaming away from MCP ADC development.
2026-04-21 Fixed CMakeLists
2026-04-21 Rolled back for just ADC stuff.
2026-04-21 Fixed PWM init order
2026-05-04 Update CMakeLists.txt to include new source files and configure UART settings; remove outdated schematic PDF.
2026-05-05 Refactor calibration plan documentation to streamline content and focus on essential calibration parameters. Removed extensive details on stages and procedures, retaining only critical information re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
2026-05-06 [untested] Started compartmentalizing GPIO inits for MPHB
2026-05-06 Added files that were already here to GIT
2026-05-06 up-to-date [streaming broken]
2026-05-06 Fixed MCLK, integrated PWM to streaming code, working on script and data output.
2026-05-06 fixed scan overwrite.
2026-05-07 Both ADCs working!
2026-05-07 CDC user input started. Starting dual-ADC operation.
2026-05-07 Got rid of finite DMA cycles. User break required.
2026-05-07 Both ADCs streaming simultaneously (I think)
2026-05-07 Script now streams for 5 seconds.
2026-05-07 Can plot multiple logs in succession with numeric input
2026-05-09 Starting multiphase
2026-05-09 Working with two phases!
2026-05-09 Starting shell
2026-05-09 Fixed backspace
2026-05-09 Shell improvements [rstream end still broken!]
2026-05-09 Fixed rstream exit.
2026-05-09 ADC readout commands 'r0' and 'r1' working!
2026-05-09 [doesn't work] sample-by-sample ictl
2026-05-09 app stuff
2026-05-10 Programmable current supply!
2026-05-10 Fixes and functionalities
2026-05-10 Init and ADC printing bug fixes
2026-05-10 [commit fix!] Forgot to add core1 code.
2026-05-10 ADC read default value
2026-05-10 Corrected sign extension for ADC prints
2026-05-10 Updated script to interact with "app" shell
2026-05-10 Timestamps auto-generate
2026-05-10 irun now **enables** the phases in addition to disabling.
2026-05-10 Dithering and PI control.
2026-05-10 Enforce bounds on the level.
2026-05-10 Compiled Version 0 Release
2026-05-10 Added fourth MPHB card. Fixed "level" command to take float argument
2026-05-10 AI Documentation for software dev
2026-05-11 Drop unused MSIF_Docs markdowns + ignore personal scratch dir
    Removed:
    - MSIF_dev/MSIF_Docs/calibration_plan.md
    - MSIF_dev/MSIF_Docs/user_manual.md
    Added to .gitignore:
    - MSIF_dev/MSIF_Docs/whatever/ — personal scratch, keep untracked
2026-05-11 Fixed lie in the AI docs.
2026-05-11 Fixed more lies in the AI documentation
2026-05-12 Example log files
2026-05-12 Added VSNS Amp init to adpc_init().
2026-06-23 MSIF: reconcile msif_adc.c with updated MCP driver
    - Pass -1 for the new mclk_pin arg in mcp_spi_init (we use the chip's
    internal clock; mcp_mclk_init is never called).
    - Drop the now-obsolete s_adc.spi workaround — the upstream driver now
    stores the spi instance pointer itself.
    - File-header doc comment was previously stripped by Cursor; leaving
    stripped per archi's call.
